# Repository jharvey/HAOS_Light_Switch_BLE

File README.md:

## Overview 

**Reference Designs** based on 
- Mohamed-U3 PCB V3.1 of hackaBLE https://github.com/Mohamed-U3/ElectronutLabs-hackaBLE
- Reference code https://github.com/agittins/NarfButt\
- uses https://github.com/bouni/kicad-jlcpcb-tools for JLCPCB intergration.
- uses https://raw.githubusercontent.com/CDFER/

**Features**

- Raytac MDBT42 based on Nordic Semiconductor's nRF52832 SOC with chip antenna
- 3 LED's
- Button user configurable, set as RESET by default
- SWD programming headers
- CR2032 power
- Button up
- Button down

**nRF52 IO**
- P0.00 32.768KHz with 12pF load caps
- P0.01 32.768KHz with 12pF load caps
- P0.11 Up push button
- P0.12 Down push button
- P0.17 Red LED via 33 ohm pull up at about 5ma when on. 
- P0.18 Green LED via 10 ohm pull up at about 5ma when on. 
- P0.19 White LED via 10 ohm pull up at about 5ma when on. 
- P0.21 Reset push button via 10k pull up resistor. 
- Ant 0.8pF and 3.9nH filter to PCB trace antenna. 
- XC1 ABM8-32.000MHZ-B2-T3 with 12pF load caps
- XC2 ABM8-32.000MHZ-B2-T3 with 12pF load caps
- VDD 4.7uF, 0.1uF, 0.1uF caps to gnd
- DEC1 0.1uF to Ggnd
- DEC2 No connection
- DEC3 No connection
- DEC4 to DCC via inductors listed below. 
- DCC 10uH to 15nH to DEC4 to 1uF to gnd
- SWD is connected to a dedicated connector with VDD and gnd
- All unused pins are routed to a connector which allows probing with a scope or adding prototype features.

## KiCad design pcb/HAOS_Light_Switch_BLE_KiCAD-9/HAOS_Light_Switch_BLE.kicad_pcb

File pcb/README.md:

# HAOS_Light_Switch_BLE
A compact Nordic nRF52832 BLE module for HAOS light switch signals.

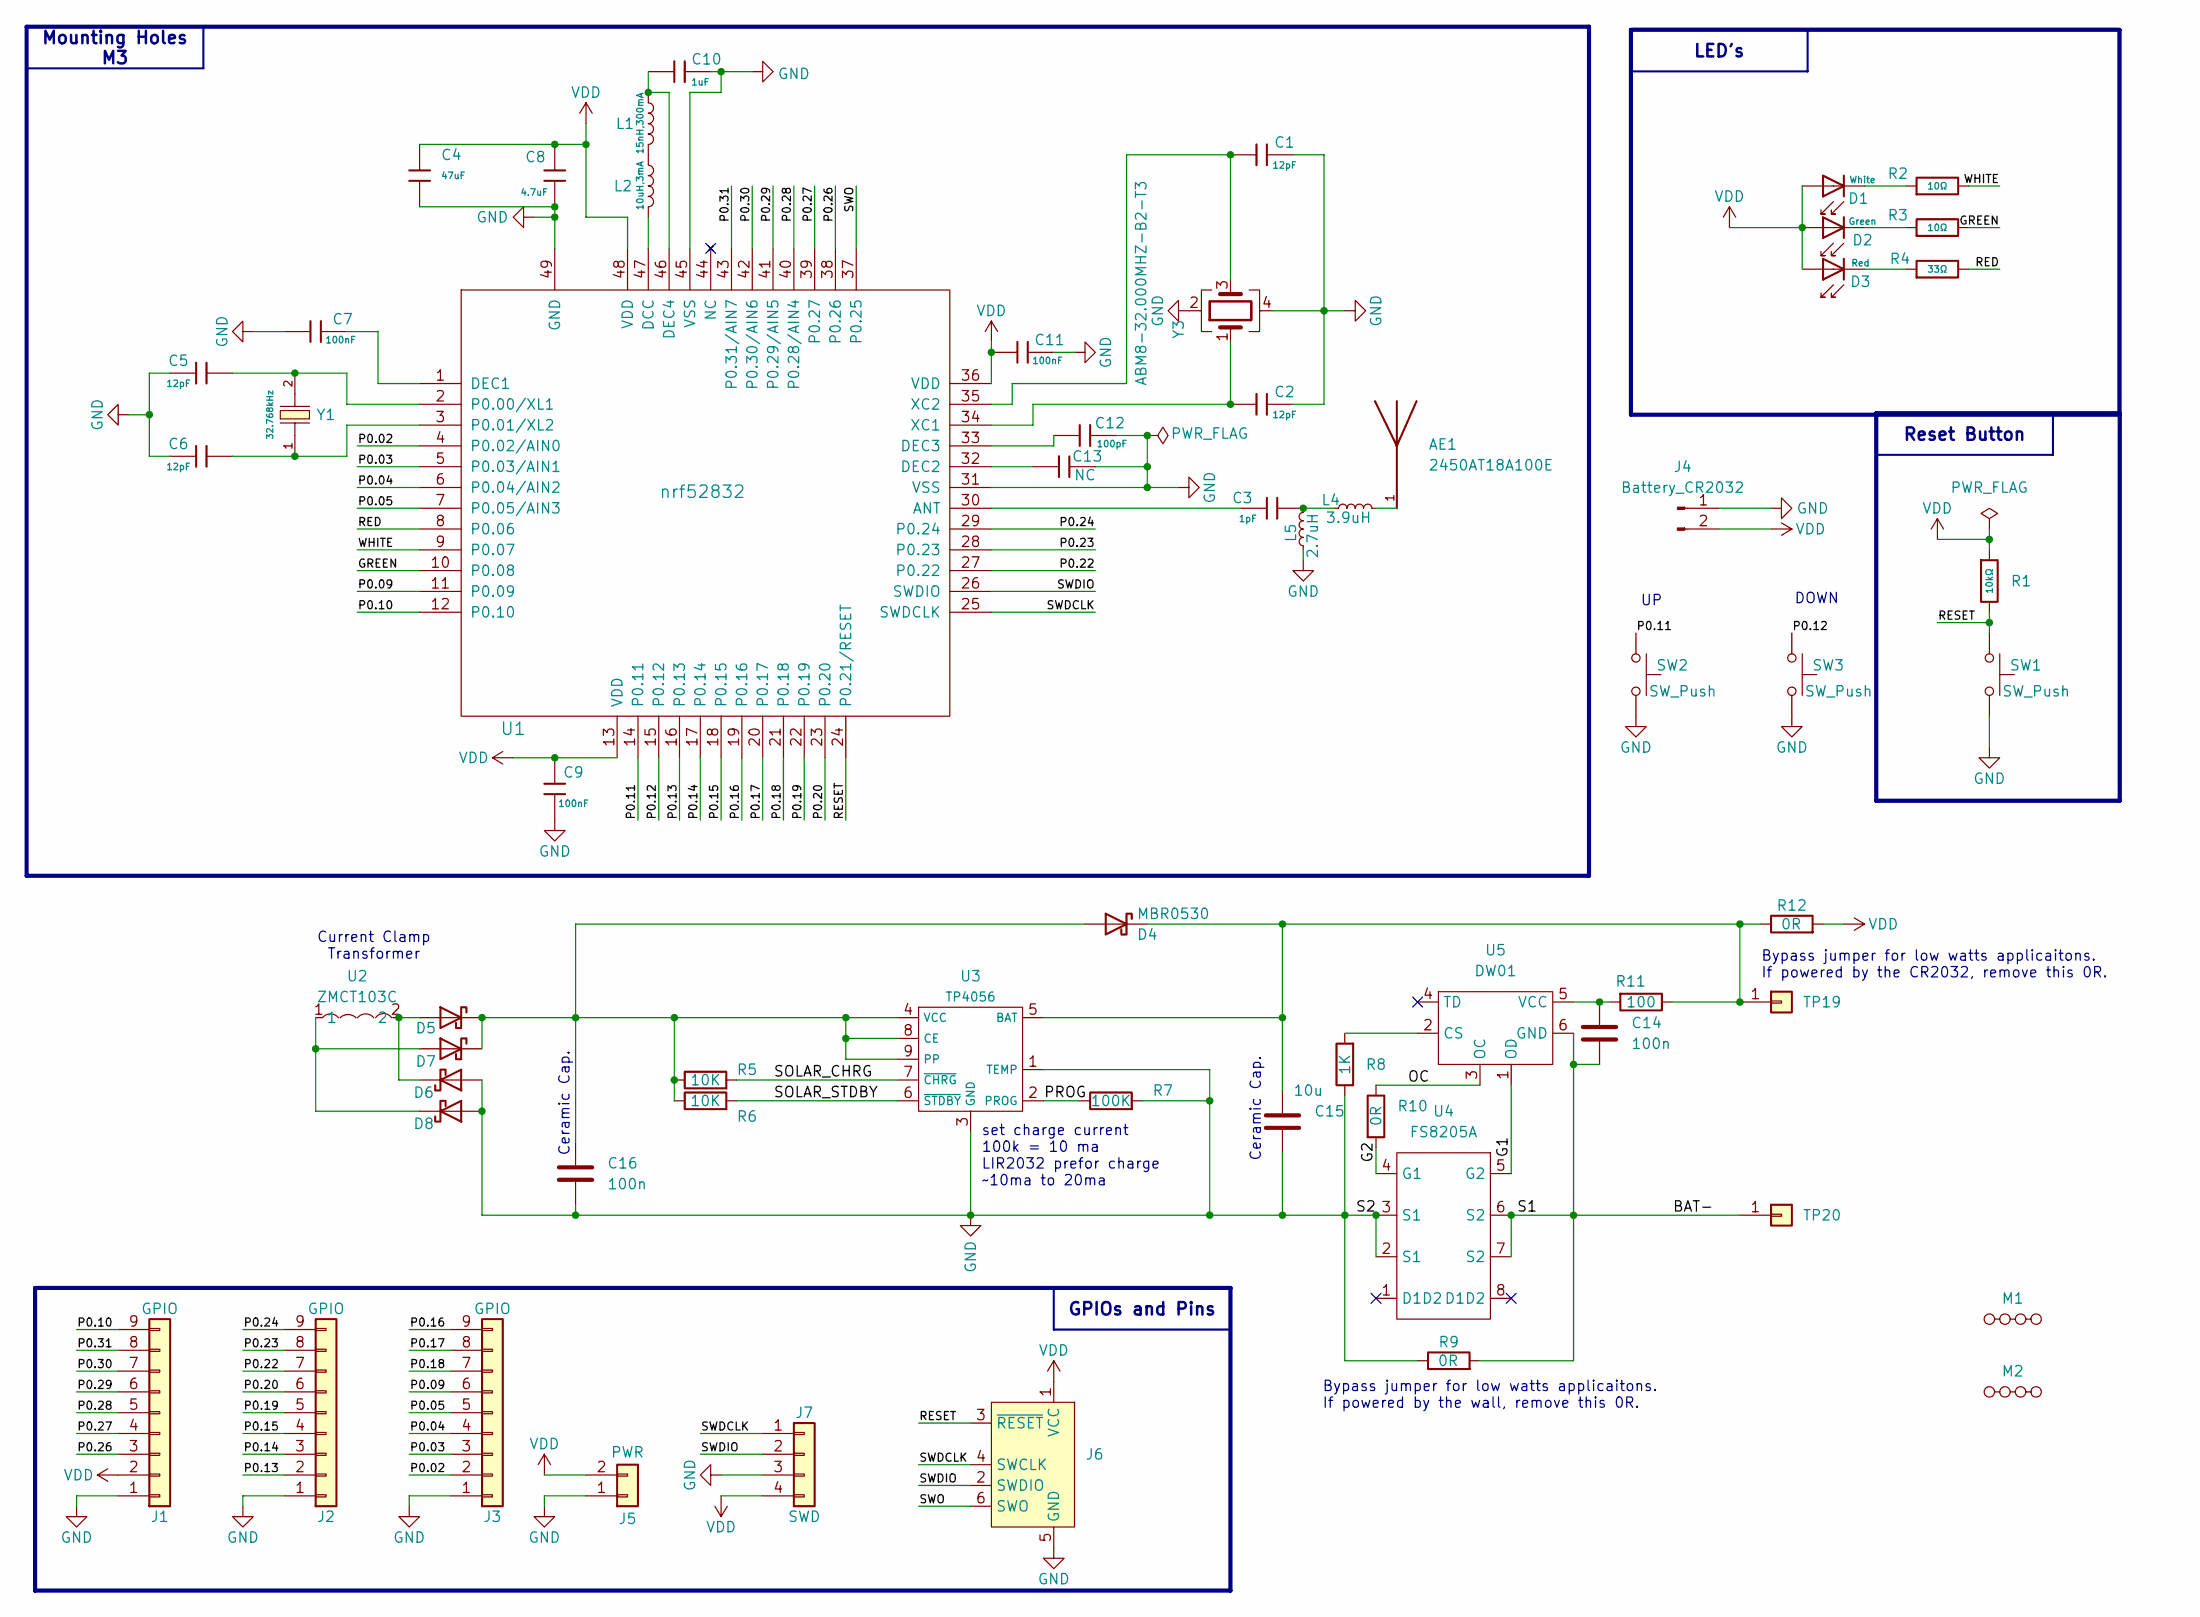
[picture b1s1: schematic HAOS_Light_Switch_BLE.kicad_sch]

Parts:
AE1: 2450AT18A100E; ANTC3216X140N; PARTREV 1.3
C1, C2, C5, C6: 12pF; C_0402; Voltage Rated 50V; Tolerance ±5%; Part 0402CG120J500NT; LCSC C1547
C3: 1pF; C_0402; Voltage Rated 50V; LCSC C1550
C4: 47uF; C_0805; LCSC C124129
C7, C9, C11: 100nF; C_0402; Voltage Rated 50V; Tolerance ±10%; Part CL05B104KB54PNC; LCSC C307331
C8: 4.7uF; C_0603; Voltage Rated 16V; Tolerance ±10%; Part CL10A475KO8NNNC; LCSC C19666
C10: 1uF; C_0603; Voltage Rated 50V; Tolerance ±10%; Part CL10A105KB8NNNC; LCSC C15849
C12: 100pF; C_0402; Voltage Rated 50V; Tolerance ±5%; Part 0402CG101J500NT; LCSC C1546
C13: NC; C_0402_1005Metric_Pad0.74x0.62mm_HandSolder
C14, C16: 100n; C_0603_1608Metric; LCSC C14663
C15: 10u; C_0603_1608Metric; LCSC C194427
D1: White; D_0805; Part KT-0805W; LCSC C34499
D2: Green; D_0805; Part KT-0805G; LCSC C2297
D3: Red; D_0805; Forward Voltage (VF) 1.6V~2.6V; Part NCD0805R1; LCSC C84256
D4, D5, D6, D7, D8: MBR0530; D_SOD-123; LCSC C77336
J1, J2, J3: GPIO; PinHeader_1x09_P2.54mm_Vertical
J4: Battery_CR2032; BatteryHolder_MYOUNG_BS-07-A1BJ001_CR2032; LCSC C2979167
J5: PWR; PinHeader_1x02_P1.00mm_Vertical
J6: Conn_ARM_SWD_TagConnect_TC2030-NL; Tag-Connect_TC2030-IDC-NL_2x03_P1.27mm_Vertical
J7: SWD; PinHeader_1x04_P2.54mm_Vertical
L1: 15nH,300mA; L_0402; Tolerance ±5%; Part SDCL1005C15NJTDF; LCSC C27143
L2: 10uH,3mA; L_0603; Tolerance ±10%; Part SDFL1608S100KTF; LCSC C1035
L4: 3.9uH; L_0402_1005Metric_Pad0.77x0.64mm_HandSolder; LCSC C98062
L5: 2.7uH; L_0402_1005Metric_Pad0.77x0.64mm_HandSolder; LCSC C91239
M1, M2: MouseBites, Cosmetic, JLCPCB, 1.6mm
R1: 10kΩ; R_0603; Overload Voltage (Max) 75V; Tolerance ±1%; Part 0603WAF1002T5E; LCSC C25804
R2, R3: 10Ω; R_0603; Overload Voltage (Max) 75V; Tolerance ±1%; Part 0603WAF100JT5E; LCSC C22859
R4: 33Ω; R_0603; Overload Voltage (Max) 75V; Tolerance ±1%; Part 0603WAF330JT5E; LCSC C23140
R5, R6: 10K; R_0603_1608Metric; LCSC C25804
R7: 100K; R_0603_1608Metric; LCSC C25803
R8: 1K; R_0603_1608Metric; LCSC C21190
R9, R10, R12: 0R; R_0603_1608Metric; LCSC C21189
R11: 100; R_0603_1608Metric; LCSC C4184
SW1, SW2, SW3: SW_Push; SW_SPST_PTS810; LCSC C2888429
TP19, TP20: CONN_01; PinHeader_1x01_P1.00mm_Vertical; LCSC DNP
U1: nrf52832; QFN-48-1EP_6x6mm_P0.4mm_EP4.4x4.4mm_ThermalVias; LCSC C77540
U2: ZMCT103C; XFMR-TH_ZMCT103C; LCSC Part C94571
U3: TP4056; ESOP-8_L4.9-W3.9-P1.27-LS6.0-BL-EP; LCSC C16581
U4: FS8205A; TSSOP-8_L4.4-W3.0-P0.65-LS6.4-BL-2; LCSC C16052
U5: DW01; SOT-23-6_L2.9-W1.6-P0.95-LS2.8-BL; LCSC C351410
Y1: Q13FC1350000400; FC-135R_L3.2-W1.5; Frequency Tolerance ±20ppm; Part Q13FC13500004; LCSC C32346
Y3: ABM8-32.000MHZ-B2-T3; Crystal_SMD_Abracon_ABM8AIG-4Pin_3.2x2.5mm; PARTREV 44041; LCSC C1986513

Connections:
/BAT-: C14.2, R9.2, TP20.1, U4.6 (S2), U4.7 (S2), U5.6 (GND)
/G1: U4.5 (G2), U5.1 (OD)
/G2: R10.2, U4.4 (G1)
/GREEN: R3.2, U1.10 (P0.08)
/OC: R10.1, U5.3 (OC)
/P0.02: J3.2, U1.4 (P0.02/AIN0)
/P0.03: J3.3, U1.5 (P0.03/AIN1)
/P0.04: J3.4, U1.6 (P0.04/AIN2)
/P0.05: J3.5, U1.7 (P0.05/AIN3)
/P0.09: J3.6, U1.11 (P0.09)
/P0.10: J1.9, U1.12 (P0.10)
/P0.11: SW2.1, U1.14 (P0.11)
/P0.12: SW3.1, U1.15 (P0.12)
/P0.13: J2.2, U1.16 (P0.13)
/P0.14: J2.3, U1.17 (P0.14)
/P0.15: J2.4, U1.18 (P0.15)
/P0.16: J3.9, U1.19 (P0.16)
/P0.17: J3.8, U1.20 (P0.17)
/P0.18: J3.7, U1.21 (P0.18)
/P0.19: J2.5, U1.22 (P0.19)
/P0.20: J2.6, U1.23 (P0.20)
/P0.22: J2.7, U1.27 (P0.22)
/P0.23: J2.8, U1.28 (P0.23)
/P0.24: J2.9, U1.29 (P0.24)
/P0.26: J1.3, U1.38 (P0.26)
/P0.27: J1.4, U1.39 (P0.27)
/P0.28: J1.5, U1.40 (P0.28/AIN4)
/P0.29: J1.6, U1.41 (P0.29/AIN5)
/P0.30: J1.7, U1.42 (P0.30/AIN6)
/P0.31: J1.8, U1.43 (P0.31/AIN7)
/PROG: R7.1, U3.2 (PROG)
/RED: R4.2, U1.8 (P0.06)
/RESET: J6.3 (~RESET), R1.2, SW1.1, U1.24 (P0.21/RESET)
/SOLAR_CHRG: R5.2, U3.7 (~CHRG)
/SOLAR_STDBY: R6.2, U3.6 (~STDBY)
/SWDCLK: J6.4 (SWCLK), J7.1, U1.25 (SWDCLK)
/SWDIO: J6.2 (SWDIO), J7.2, U1.26 (SWDIO)
/SWO: J6.6 (SWO), U1.37 (P0.25)
/WHITE: R2.2, U1.9 (P0.07)
GND: C1.1, C2.1, C4.2, C5.1, C6.1, C7.1, C8.1, C9.1, C10.2, C11.2, C12.2, C13.1, C15.2, C16.2, D7.2 (A), D8.2 (A), J1.1, J2.1, J3.1, J4.1, J5.1, J6.5 (GND), J7.3, L5.1, R7.2, R8.1, R9.1, SW1.2, SW2.2, SW3.2, U1.31 (VSS), U1.45 (VSS), U1.49 (GND), U3.1 (TEMP), U3.3 (GND), U4.2 (S1), U4.3 (S1), Y3.2, Y3.4
unnamed: AE1.1, L4.2
unnamed: C3.2, L4.1, L5.2
unnamed: D1.1, R2.1
unnamed: D2.1, R3.1
unnamed: D3.1, R4.1
unnamed: C16.1, D4.2 (A), D5.1 (K), D6.1 (K), R5.1, R6.1, U3.4 (VCC), U3.8 (CE), U3.9 (PP)
unnamed: C15.1, D4.1 (K), R11.1, R12.1, TP19.1, U3.5 (BAT)
unnamed: D5.2 (A), D7.1 (K), U2.2
unnamed: D6.2 (A), D8.1 (K), U2.1
unnamed: L1.2, L2.1
unnamed: C3.1, U1.30 (ANT)
unnamed: L2.2, U1.47 (DCC)
unnamed: C7.2, U1.1 (DEC1)
unnamed: C13.2, U1.32 (DEC2)
unnamed: C12.1, U1.33 (DEC3)
unnamed: C10.1, L1.1, U1.46 (DEC4)
unnamed: C5.2, U1.2 (P0.00/XL1), Y1.2
unnamed: C6.2, U1.3 (P0.01/XL2), Y1.1
unnamed: C2.2, U1.34 (XC1), Y3.1
unnamed: C1.2, U1.35 (XC2), Y3.3
unnamed: R8.2, U5.2 (CS)
unnamed: C14.1, R11.2, U5.5 (VCC)
VDD: C4.1, C8.2, C9.2, C11.1, D1.2, D2.2, D3.2, J1.2, J4.2, J5.2, J6.1 (VCC), J7.4, R1.1, R12.2, U1.13 (VDD), U1.36 (VDD), U1.48 (VDD)

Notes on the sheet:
set charge current 100k = 10 ma LIR2032 prefor charge ~10ma to 20ma
Ceramic Cap.
Bypass jumper for low watts applicaitons. If powered by the wall, remove this 0R.
Bypass jumper for low watts applicaitons. If powered by the CR2032, remove this 0R.
DOWN
Current Clamp Transformer
LED's
GPIOs and Pins
Reset Button
Mounting Holes M3

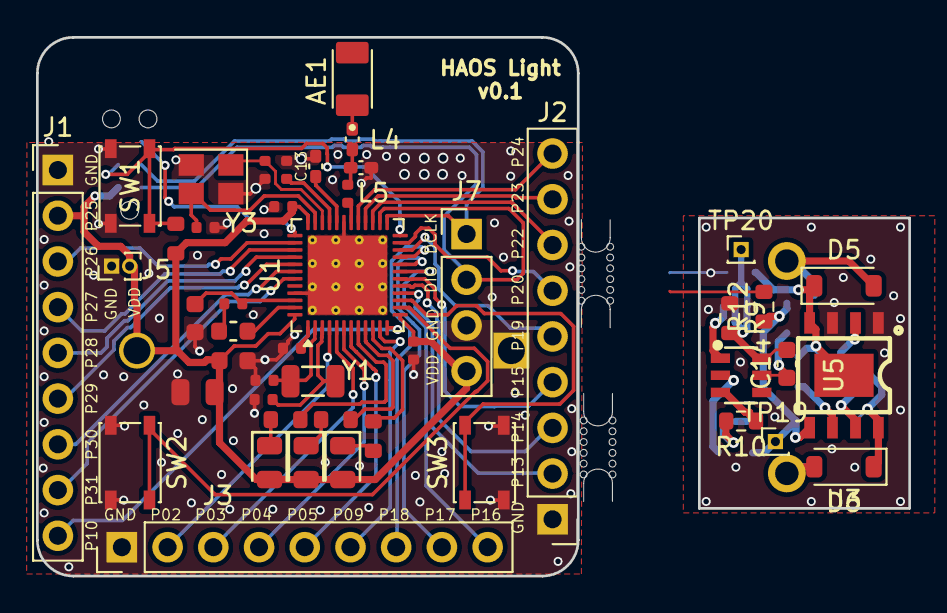
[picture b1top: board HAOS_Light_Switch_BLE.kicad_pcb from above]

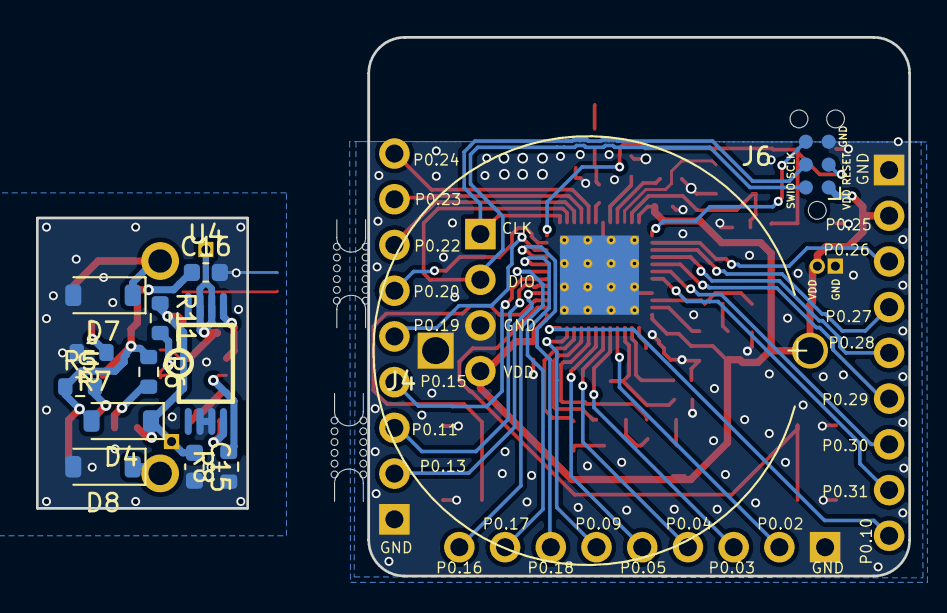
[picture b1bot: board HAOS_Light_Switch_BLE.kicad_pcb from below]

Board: 2 copper layers, 48.5 x 29.9 mm, 62 parts (14 on the bottom side), 63 nets.

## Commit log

2026-01-18 Revise README for repository migration and updates
    Updated README to reflect repository migration to GitLab and revised content for clarity.
2026-01-18 Revise README.md for nRF52 IO details
    Updated IO section with detailed specifications and connections.
2026-01-18 Update README with JLCPCB integration details
    Added information about JLCPCB integration tools.
2026-01-18 Revise LED specifications and integration links
    Updated LED descriptions and integration references in README.
2026-01-19 Initial PCB commit.
2026-01-19 Updated antenna
2026-01-19 updated per DRC
2026-01-19 Potential 1st spin.
2026-01-19 Added more documentation.
2026-01-19 added Tag-Connect programming connector
2026-01-19 Added C4 to help mitigate brown out potential during radio transmissions.
2026-01-20 Added SWO to Tag-Connect
2026-01-24 deleted old unused project file.
2026-01-24 draft update
2026-01-24 File Name correction
2026-01-25 added neutral current clamp draft copy of schematic.
2026-01-27 Draft AC power sniffer
2026-01-27 Draft
2026-01-28 Draft updated trace width
2026-01-29 Change R7 limiting charge current to 10ma for LIR2032 charging.
